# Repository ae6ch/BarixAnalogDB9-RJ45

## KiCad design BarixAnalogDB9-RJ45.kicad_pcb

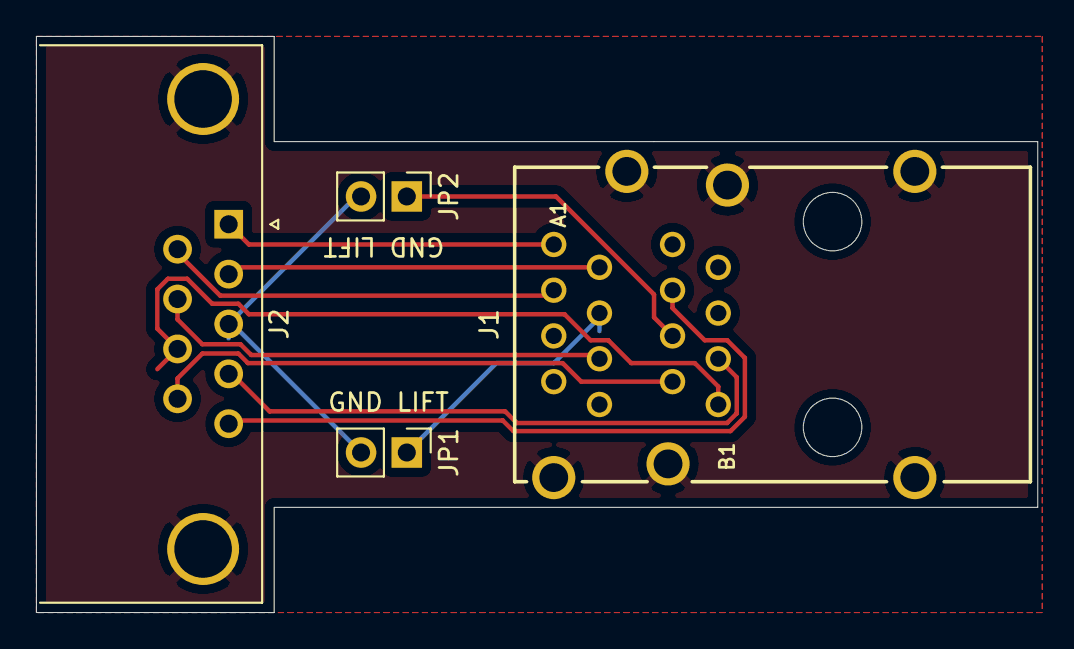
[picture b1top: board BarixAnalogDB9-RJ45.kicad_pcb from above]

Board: 2 copper layers, 55.6 x 32.0 mm, 4 parts (0 on the bottom side), 12 nets.

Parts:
J1: Barix Input; 615016240521
J2: DB9_Male; DSUB-9_Male_Horizontal_P2.77x2.84mm_EdgePinOffset7.70mm_Hou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
JP1, JP2: GND LIFT; PinHeader_1x02_P2.54mm_Vertical

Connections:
GND: J1.S1, J1.S2, J1.S3, J1.S4, J1.S5, J1.S6, J2.0
unnamed: J1.A1, J2.1
unnamed: J1.A2, J2.2
unnamed: J1.A3, J2.6
unnamed: J1.A4, JP1.1
unnamed: J1.A6, J2.7
unnamed: J1.B1, J2.8
unnamed: J1.B2, J2.9
unnamed: J1.B3, J2.4
unnamed: J1.B4, JP2.1
unnamed: J1.B6, J2.5
unnamed: J2.3, JP1.2, JP2.2

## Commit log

2021-07-06 initial
2021-07-22 finished
